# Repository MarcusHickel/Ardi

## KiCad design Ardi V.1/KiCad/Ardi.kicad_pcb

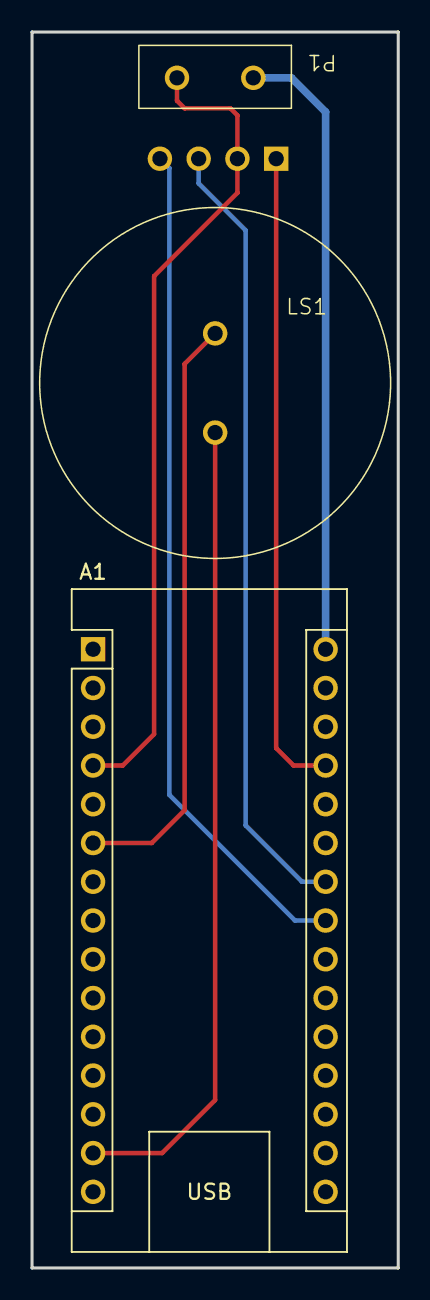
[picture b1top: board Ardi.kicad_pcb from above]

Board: 2 copper layers, 24.0 x 81.0 mm, 4 parts (1 on the bottom side), 7 nets.

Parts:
A1: Arduino_Nano_v3.x; Arduino_Nano
LS1: Speaker; AT-1224-TWT-5V-2-R
P1: TERM BLOCK HDR 2POS 90DEG 5MM
U1: DFROBOT_BMP_280; DFROBOT_BMP280

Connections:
+5V: A1.27 (+5V), U1.1 (VCC)
GND: A1.4 (GND), P1.2, U1.2 (GND)
unnamed: A1.23 (A4), U1.4 (SDA)
unnamed: A1.24 (A5), U1.3 (SCL)
unnamed: A1.6 (D3), LS1.2
unnamed: A1.14 (D11), LS1.1
unnamed: A1.30 (VIN), P1.1

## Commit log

2024-06-28 First Commit
    Yep thats right, did first try
2024-08-08 Added Versions
2024-08-08 Moved and named KiCad folder
2024-08-08 Added boot tests
    Note that BMP280 and SDcard 'Fail' but still actually work. Not sure why
2024-08-08 I2C Test
    Checks for BMP280 and ICM20948 at their respective addresses
2024-08-09 Updated baroemeter test
    Works now. bmp.begin() returns an Enum that is 0 when working fine. Also a delay is needed in front of the pressure call for some reason.
2024-08-09 Updated ICM20948 test
2024-08-09 Updated SDCard test
    Usual issue was that the wire was loose. If everything fails check that first
2024-08-09 Renamed barometer to BMP280
2024-08-09 Updated test_led
2024-08-20 Ardi V.2 Testing
2024-08-20 Added ESP32-s3 datasheets
2024-08-20 Created Ardi V.3 Project
    +GPS +Telemetry downlink
2024-08-23 Added hardware
    Schematics, and footprints using KiCAD 8.0
2024-08-25 Added LED and BMP280 test to main code
2024-08-25 Moved Arduino data sheets
2024-08-25 Added ICM20984 test to main
    Rudimentary, can be made more robust
2024-08-26 Added SDCARD Test
    Not sure how reliable it is
2024-08-26 Added NEO-M6 GPS test to main
2024-08-30 LoRa Testing
2024-09-02 Added LoRa Test with Ground station
2024-09-08 Added writing of data to SD
    GPS,Pressure,Temperature,Accel,gyro,mag data
